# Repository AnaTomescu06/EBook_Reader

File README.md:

# OpenBook – Proiect TSC 2025

## Descriere generală

**OpenBook** este un dispozitiv portabil de tip e-book reader, conceput ca soluție open-source, eficientă energetic și scalabilă. Acesta se bazează pe microcontrolerul **ESP32-C6-WROOM**, având ca funcții principale afișarea de conținut pe un ecran e-paper și monitorizarea parametrilor de mediu (temperatură, umiditate, CO2, particule).

Dispozitivul permite salvarea datelor colectate pe un card microSD și oferă control prin intermediul unor butoane fizice.

## Diagramă bloc

## Funcționalitate hardware

Dispozitivul este structurat în jurul modulului **ESP32-C3-WROOM**, care gestionează toate interfețele de comunicare cu componentele externe.

### ESP32-C3-WROOM
- Microcontroler principal cu suport pentru **Wi-Fi** și **BLE**
- Interfețe: **SPI**, **I2C**, **UART**
- Alimentare: **3.3V** prin LDO

### Sistem de alimentare
- **USB-C** pentru alimentare externă și comunicare
- **MCP73832** pentru managementul încărcării bateriei Li-Po
- **LDO 3.3V** pentru alimentarea logicii
- **DC-DC 5V** pentru alimentarea senzorilor PM și CO2

### Senzori
- **BME680** (I2C, 3.3V) - temperatură, umiditate, gaze
- **MH-Z19B** (UART, 5V) - CO2
- **PMSA003** (UART, 5V) - particule fine (PM2.5)

### Ecran
- **E-paper monocrom 1.5''** cu rezoluție 200x200 px
- Interfață SPI comună cu cardul SD

### Card SD
- Slot microSD pentru stocarea de date/text
- Interfață SPI

### Butoane
- 3 butoane tactile conectate la pinii GPIO pentru interacțiune cu utilizatorul

## Bill of Materials (BOM)

| Part | Device | Datasheet |
|------|--------|-----------|
| CHG_LED | ADAFRUIT_LEDCHIP-LED0603 | [ADAFRUIT_LEDCHIP-LED0603](https://www.snapeda.com/parts/KP-1608SURCK/Kingbright/view-part/?ref=search&t=LED%200603) |
| SJ1 | SJ | [SJ](https://grabcad.com/library/solder-jumpers-1) |
| EPD_C5 | EAGLE-LTSPICE_CC0402 | [EAGLE-LTSPICE_CC0402](https://www.snapeda.com/parts/PGB1010603MR/Littelfuse/view-part/?ref=eda) |
| R3 | ESP32_WROVER_EAGLE-LTSPICE_RR0402 | (https://componentsearchengine.com/part-view/R0402%201%25%20100%20K%20(RC0402FR-07100KL)/YAGEO) |
| R1_PWRUSB | ESP32_WROVER_EAGLE-LTSPICE_RR0402 | (https://componentsearchengine.com/part-view/R0402%201%25%20100%20K%20(RC0402FR-07100KL) |
| C4_USB | EAGLE-LTSPICE_CC0402 | [EAGLE-LTSPICE_CC0402](https://componentsearchengine.com/part-view/CC0402MRX5R5BB106/YAGEO) |
| C1, C2, C6, C8, C9, C10, C_DELAY | ESP32_WROVER_EAGLE-LTSPICE_CC0402 | [ESP32_WROVER_EAGLE-LTSPICE_CC0402](https://componentsearchengine.com/part-view/CC0402MRX5R5BB106/YAGEO) |
| C3 | RCL_CPOL-EUCT3528 | [RCL_CPOL-EUCT3528](https://componentsearchengine.com/part-view/CC0402MRX5R5BB106/YAGEO) |
| R1, R1_PINH, R1_PINH1, R2_PINH, R2_PINH1, R4, R5, R6, R7, R8, R9, R10, R_BOOT, R_CHANGE, R_CL1, R_RESET | ESP32_WROVER_EAGLE-LTSPICE_RR0402 | [ESP32_WROVER_EAGLE-LTSPICE_RR0402](https://componentsearchengine.com/part-view/R0402%201%25%20100%20K%20(RC0402FR-07100KL)/YAGEO) |
| C7 | ESP32_WROVER_EAGLE-LTSPICE_CC0402 | [ESP32_WROVER_EAGLE-LTSPICE_CC0402](https://componentsearchengine.com/part-view/CC0402MRX5R5BB106/YAGEO) |
| J4 | 112A-TAAR-R03_ATTEND | [112A-TAAR-R03_ATTEND](https://store.comet.srl.ro/Catalogue/Product/43497/) |
| R_CAPACITOR | ESP32_WROVER_EAGLE-LTSPICE_RR0402 | [ESP32_WROVER_EAGLE-LTSPICE_RR0402](https://componentsearchengine.com/part-view/R0402%201%25%20100%20K%20(RC0402FR-07100KL)/YAGEO) |
| C5 | ESP32_WROVER_EAGLE-LTSPICE_CC0402 | [ESP32_WROVER_EAGLE-LTSPICE_CC0402](https://componentsearchengine.com/part-view/CC0402MRX5R5BB106/YAGEO) |
| EPD_C6, EPD_C7, EPD_C8, EPD_C9, EPD_C10, EPD_C11, EPD_C12 | EAGLE-LTSPICE_CC0402 | [EAGLE-LTSPICE_CC0402](https://componentsearchengine.com/part-view/CC0402MRX5R5BB106/YAGEO) |
| EPD_C1, EPD_C2 | ESP32_WROVER_EAGLE-LTSPICE_CC0402 | [ESP32_WROVER_EAGLE-LTSPICE_CC0402](https://componentsearchengine.com/part-view/CC0402MRX5R5BB106/YAGEO) |
| R2 | ESP32_WROVER_EAGLE-LTSPICE_RR0402 | [ESP32_WROVER_EAGLE-LTSPICE_RR0402](https://componentsearchengine.com/part-view/R0402%201%25%20100%20K%20(RC0402FR-07100KL)/YAGEO) |
| R1_BAT | ESP32_WROVER_EAGLE-LTSPICE_RR0402 | [ESP32_WROVER_EAGLE-LTSPICE_RR0402](https://componentsearchengine.com/part-view/R0402%201%25%20100%20K%20(RC0402FR-07100KL)/YAGEO) |
| Q1, Q2 | ESP32_WROVER_SPARKFUN-DISCRETESEMI_MOSFET_PCH-DMG2305UX-7 | [ESP32_WROVER_SPARKFUN-DISCRETESEMI_MOSFET_PCH-DMG2305UX-7](https://componentsearchengine.com/part-view/DMG2305UX-7/Diodes%20Incorporated) |
| R2_BAT | ESP32_WROVER_EAGLE-LTSPICE_RR0402 | [ESP32_WROVER_EAGLE-LTSPICE_RR0402](https://componentsearchengine.com/part-view/R0402%201%25%20100%20K%20(RC0402FR-07100KL)/YAGEO) |
| C5_USB | EAGLE-LTSPICE_CC0402 | [EAGLE-LTSPICE_CC0402](https://componentsearchengine.com/part-view/CC0402MRX5R5BB106/YAGEO) |
| C1_BAT, C1_BAT1, C1_BAT2, C2_BAT | ESP32_WROVER_EAGLE-LTSPICE_CC0402 | [ESP32_WROVER_EAGLE-LTSPICE_CC0402](https://componentsearchengine.com/part-view/CC0402MRX5R5BB106/YAGEO) |
| C4 | ESP32_WROVER_EAGLE-LTSPICE_CC0402 | [ESP32_WROVER_EAGLE-LTSPICE_CC0402](https://componentsearchengine.com/part-view/CC0402MRX5R5BB106/YAGEO) |
| R2-USB, R2-USB1 | ESP32_WROVER_EAGLE-LTSPICE_RR0402 | [ESP32_WROVER_EAGLE-LTSPICE_RR0402](https://componentsearchengine.com/part-view/R0402%201%25%20100%20K%20(RC0402FR-07100KL)/YAGEO) |
| L1 | 744043680IND_4828-WE-TPC_WRE | [744043680IND_4828-WE-TPC_WRE](https://eu.mouser.com/ProductDetail/Wurth-Elektronik/744043680?qs=PGXP4M47uW6VkZq%252BkzjrHA%3D%3D) |
| IC1 | BD5229G-TR | [BD5229G-TR](https://componentsearchengine.com/part-view/BD5229G-TR/ROHM%20Semiconductor) |
| SENSOR2 | ESP32_WROVER_BME680_BME680 | [ESP32_WROVER_BME680_BME680](https://www.snapeda.com/parts/BME680/Bosch/view-part/?welcome=home) |
| BUTTON_CUSYOMV1 |BUTTON_CUSYOMV1 | [BUTTON_CUSYOMV1](https://industry.panasonic.com/global/en/products/control/switch/light-touch/number/evqpuj02k) |
| C10_SUPERCAP | CPH3225A | [CPH3225A](https://www.snapeda.com/parts/CPH3225A/Seiko+Instruments/view-part/?ref=snap) |
| U3 | DS3231SN# | [DS3231SN#](https://www.snapeda.com/parts/DS3231SN%23/Analog+Devices/view-part/?ref=snap) |
| U2 | ESP32-C6-WROOM-1-N8 | [ESP32-C6-WROOM-1-N8](https://www.snapeda.com/parts/ESP32-C6-WROOM-1-N8/Espressif+Systems/view-part/?ref=eda) |
| PFMF.050.1 | ESP32C6_VARISTORCN1812 | [ESP32C6_VARISTORCN1812](https://www.mouser.co.uk/ProductDetail/EPCOS-TDK/B72520T0350K062?qs=dEfas%2FXlABIszF52uu7vrg%3D%3D) |
| D2, D7 | ESP32_WROVER_AVX---SD0805S020S1R0_AVX_SD0805S020S1R0_0_0AVX_SD0805S020S1R0_0_0 | [ESP32_WROVER_AVX---SD0805S020S1R0_AVX_SD0805S020S1R0_0_0AVX_SD0805S020S1R0_0_0](https://eu.mouser.com/ProductDetail/KYOCERA-AVX/SD0805S020S1R0?qs=jCA%252BPfw4LHbpkAoSnwrdjw%3D%3D) |
| U5 | ESP32_WROVER_SPARKFUN-IC-POWER_MCP73831 | [ESP32-C6-WROOM-1-N8](https://componentsearchengine.com/part-view/MCP73831T-2ATI%2FOT/Microchip) |
| J1 | FH34SRJ-24S-0.5SH_99_ | [FH34SRJ-24S-0.5SH_99_](https://componentsearchengine.com/part-view/XC6220A331MR-G/Torex) |
| U4 | MAX17048G+T10 | [MAX17048G+T10](https://www.snapeda.com/parts/MAX17048G+T10/Analog+Devices/view-part/?ref=snap) |
| D3, D4, D5 | MBR0530 | [MBR0530](https://www.snapeda.com/parts/MBR0530/Onsemi/view-part/?ref=snap) |
| D6, D8, D9, D10, D11, D12 | PGB1010603MR | [PGB1010603MR](https://www.snapeda.com/parts/PGB1010603MR/Littelfuse/view-part/?ref=snap) |
| J3 | QWIIC_CONNECTORJS-1MM | [QWIIC_CONNECTORJS-1MM](https://www.snapeda.com/parts/PRT-14417/SparkFun%20Electronics/view-part/?ref=search&t=qwiic) |
| J2 | SAMACSYS_PARTS_USB4110-GF-A | (https://componentsearchengine.com/part-view/USB4110-GF-A/GCT%20(GLOBAL%20CONNECTOR%20TECHNOLOGY) |
| Q3 | SI1308EDL-T1-GE3 | [SI1308EDL-T1-GE3](https://componentsearchengine.com/part-view/SI1308EDL-T1-GE3/Vishay) |
| TP1, TP2, TP3, TP4, TP5, TP6, TP7, TP8, TP9, TP10, TP11, TP12, TP13, TP14, TP15, TP16, TP17 | TPTP20R | [facute de mine] |
| D1 | USBLC6-2SC6Y | [USBLC6-2SC6Y](https://www.snapeda.com/parts/USBLC6-2SC6Y/STMicroelectronics/view-part/?ref=snap) |
| U1 | W25Q512JVEIQ | [W25Q512JVEIQ](https://www.snapeda.com/parts/W25Q512JVEIQ/Winbond+Electronics/view-part/?ref=snap) |
| IC4 | XC6220A331MR-G | [XC6220A331MR-G](https://componentsearchengine.com/part-view/XC6220A331MR-G/Torex) |

## Alocare pini ESP32-C3

| Pin ESP32-C3 | Componentă  | Funcție / Motiv                     |
|--------------|-------------|-------------------------------------|
| GPIO1        | BME680      | I2C - SDA                           |
| GPIO2        | BME680      | I2C - SCL                           |
| GPIO3        | PMSA003     | UART RX pentru senzor PM           |
| GPIO4        | SD Card     | SPI Chip Select (CS)               |
| GPIO5        | E-Ink       | Data/Command                       |
| GPIO6        | E-Ink & SD  | SPI Clock (SCK)                    |
| GPIO7        | E-Ink & SD  | SPI MOSI (date)                    |
| GPIO8        | Buton 1     | Control meniu / pagină             |
| GPIO9        | Buton 2     | Control meniu / pagină             |
| GPIO10       | E-Ink       | SPI Chip Select (CS)               |
| GPIO11       | Flash ext.  | CS rezervat, neutilizat momentan   |
| GPIO12       | USB         | USB D-                             |
| GPIO13       | USB         | USB D+                             |
| GPIO18       | MH-Z19B     | UART TX pentru senzor CO2          |
| GPIO19       | Buton 3     | Confirmare / acțiune suplimentară  |

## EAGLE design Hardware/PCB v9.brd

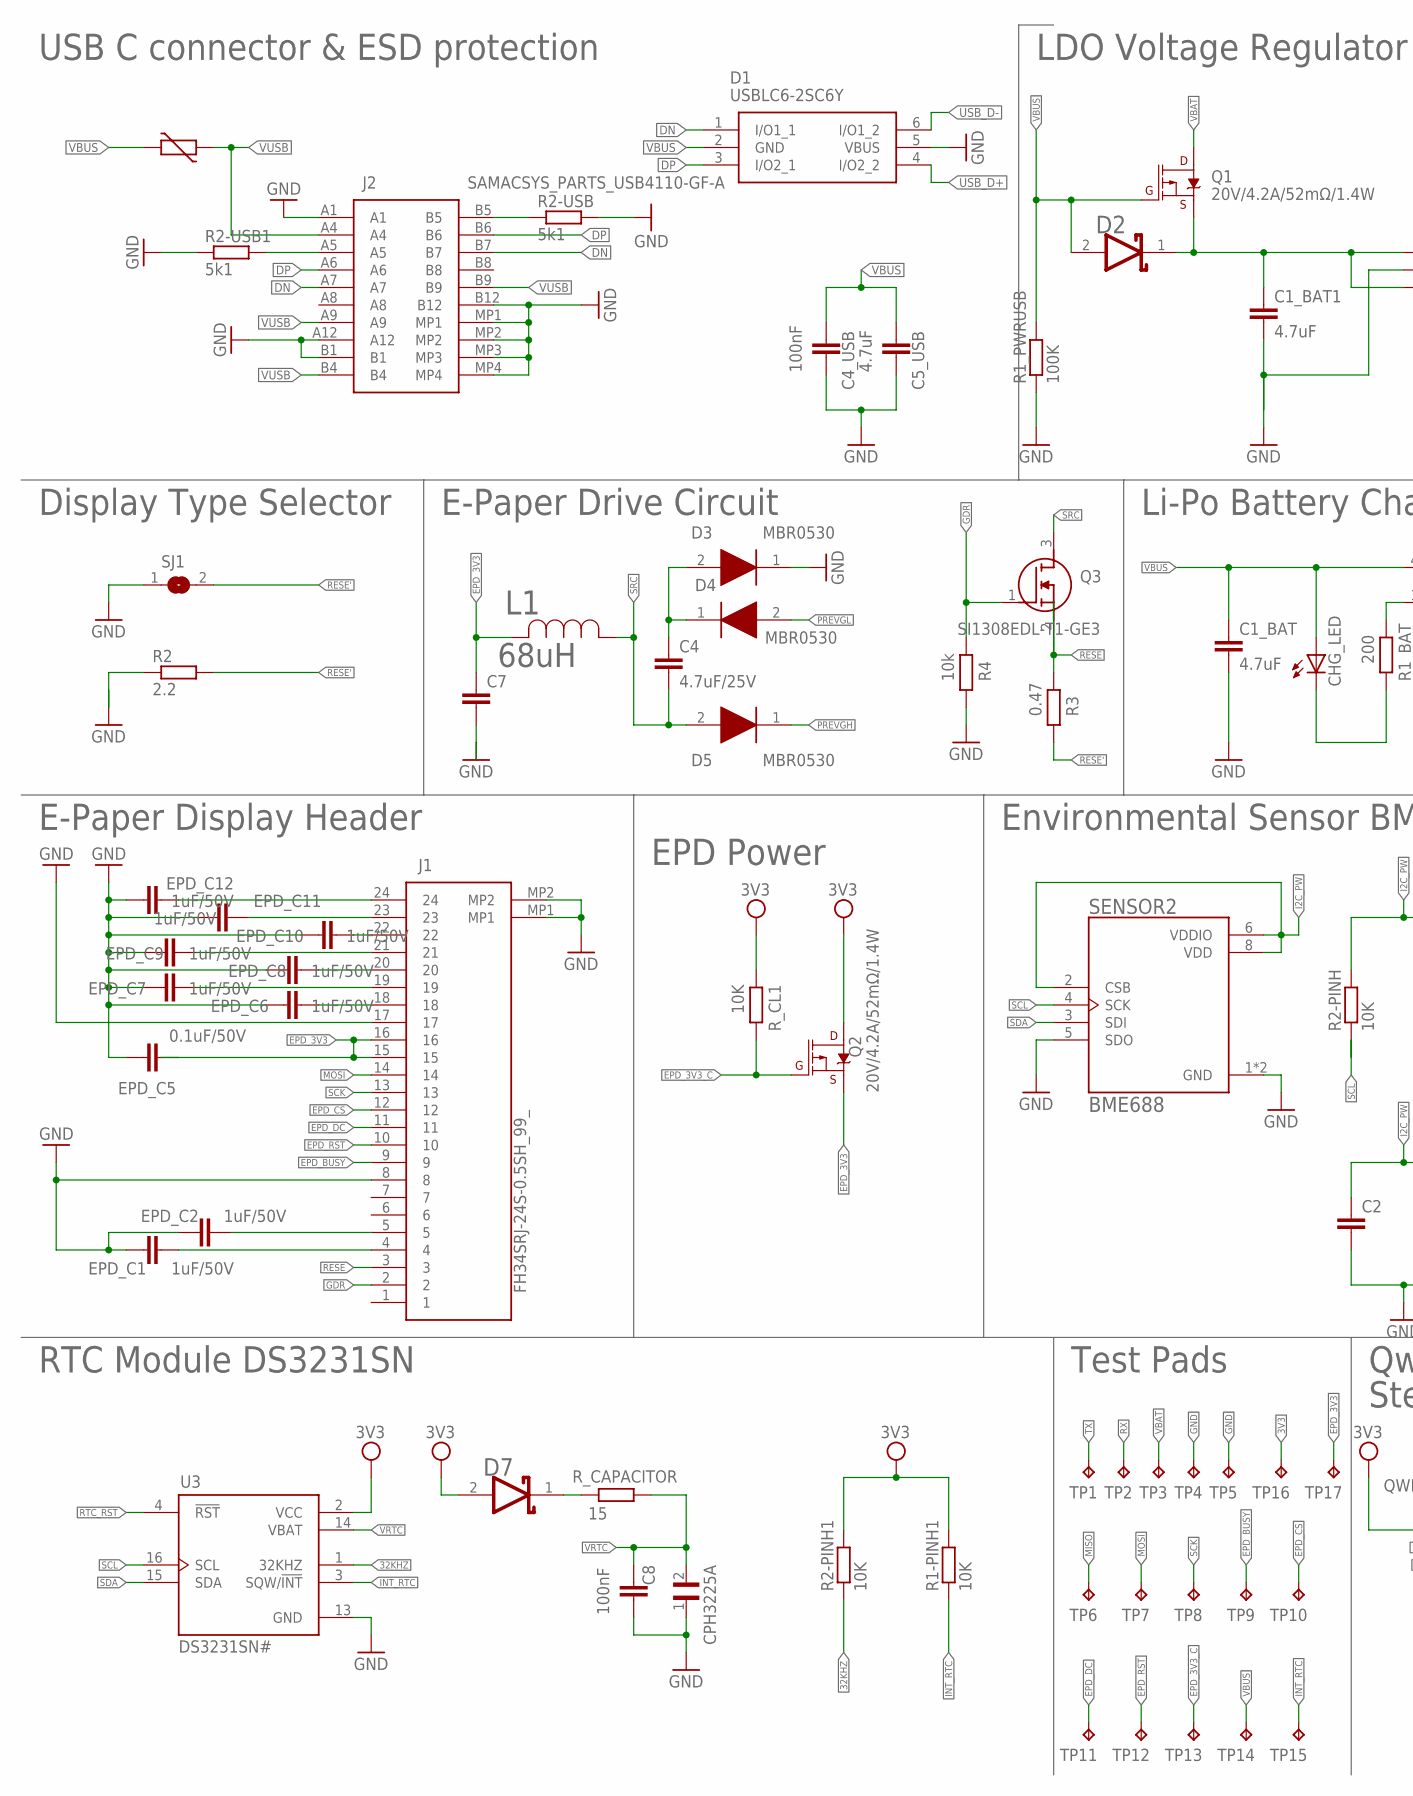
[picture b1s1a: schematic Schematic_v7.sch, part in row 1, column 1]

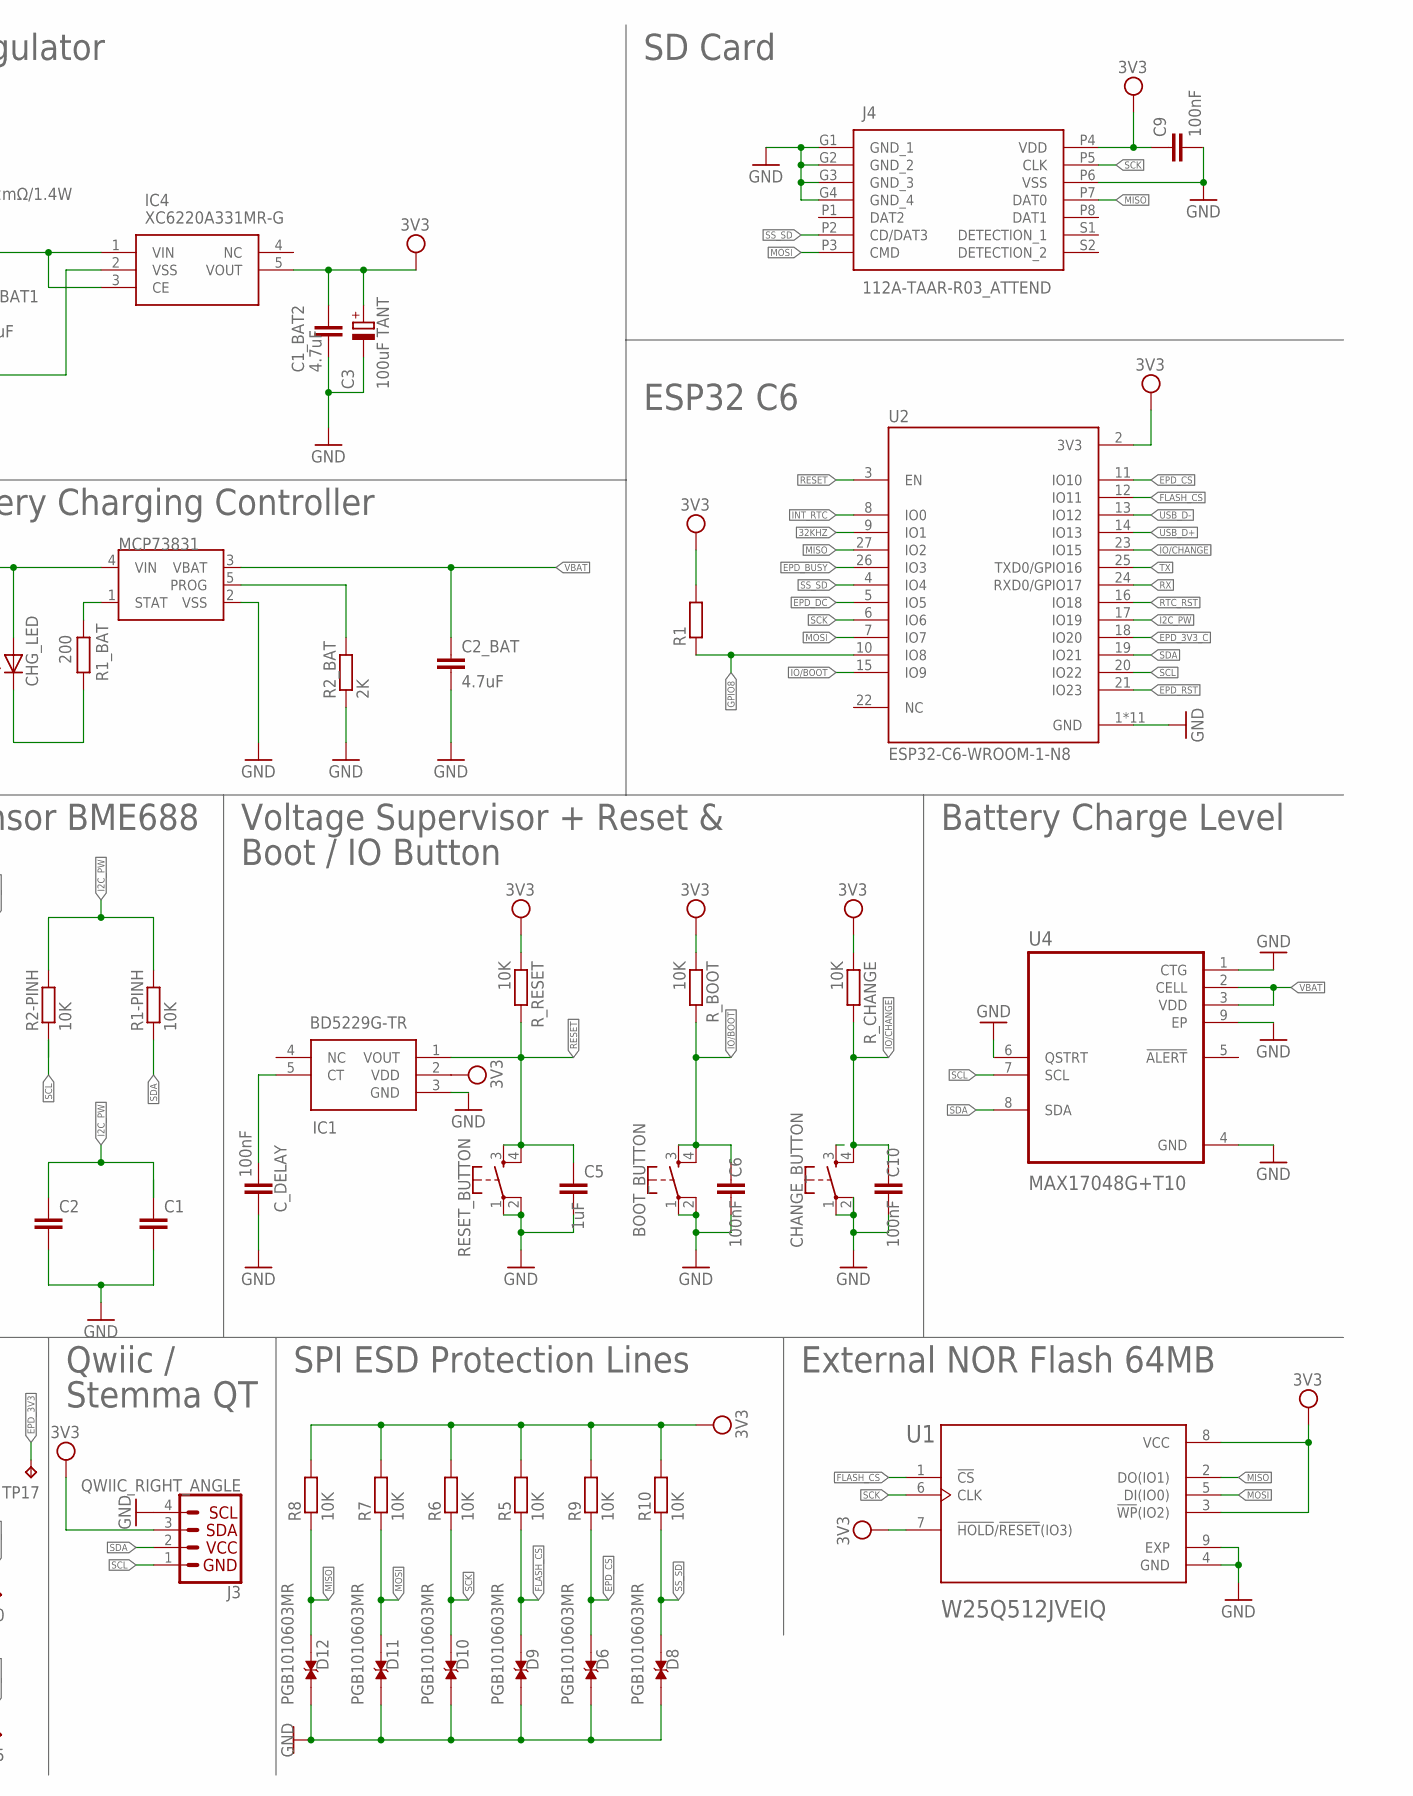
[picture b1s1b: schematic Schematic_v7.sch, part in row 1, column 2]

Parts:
BOOT_BUTTON: BUTTON_CUSYOMV1; MYBUTTON
C1, C2, C7: EAGLE-LTSPICE_CC0402; EAGLE-LTSPICE_C0402
C1_BAT, C5_USB: 4.7uF; ESP32_WROVER_EAGLE-LTSPICE_C0402
C1_BAT1, C1_BAT2, C2_BAT: 4.7uF; EAGLE-LTSPICE_C0402
C3: 100uF TANT; RCL_CT3528
C4: 4.7uF/25V; ESP32_WROVER_EAGLE-LTSPICE_C0402
C4_USB: 100nF; ESP32_WROVER_EAGLE-LTSPICE_C0402
C5: 1uF; EAGLE-LTSPICE_C0402
C6, C9, C10, C11: 100nF; EAGLE-LTSPICE_C0402
C8: CPH3225A; CAPCP3225X100N
CHANGE_BUTTON: BUTTON_CUSYOMV1; MYBUTTON
CHG_LED: ADAFRUIT_LEDCHIP-LED0603; ADAFRUIT_CHIP-LED0603
C_DELAY: 100nF; EAGLE-LTSPICE_C0402
D1: USBLC6-2SC6Y; SOT95P280X145-6N
D2, D7: ESP32_WROVER_AVX---SD0805S020S1R0_AVX_SD0805S020S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; ESP32_WROVER_AVX---SD0805S020S1R0_AVX_SD0805S020S1R0_0
D3, D4, D5: MBR0530; SOD3716X135N
D6, D8, D9, D10, D11, D12: PGB1010603MR; DIOC1608X36N
EPD_C1, EPD_C2, EPD_C6, EPD_C7, EPD_C8, EPD_C9, EPD_C10, EPD_C11, EPD_C12: 1uF/50V; ESP32_WROVER_EAGLE-LTSPICE_C0402
EPD_C5: 0.1uF/50V; EAGLE-LTSPICE_C0402
IC1: BD5229G-TR; SOT95P280X125-5N
IC4: XC6220A331MR-G; SOT95P280X120-5N
J1: FH34SRJ-24S-0.5SH_99_; FH34SRJ24S05SH99
J2: SAMACSYS_PARTS_USB4110-GF-A; SAMACSYS_PARTS_USB4110GFA
J3: QWIIC_RIGHT_ANGLE; JST04_1MM_RA
J4: 112A-TAAR-R03_ATTEND; 112ATAARR03ATTEND
L1: 68uH; IND_4828-WE-TPC_WRE
PFMF.050.1: ESP32C6_VARISTORCN1812; ESP32C6_VARISTOR_CT/CN1812
Q1, Q2: 20V/4.2A/52mΩ/1.4W; ESP32_WROVER_SPARKFUN-DISCRETESEMI_SOT23-3
Q3: SI1308EDL-T1-GE3; SOT65P210X110-3N
R1: ESP32_WROVER_EAGLE-LTSPICE_RR0402; ESP32_WROVER_EAGLE-LTSPICE_R0402
R1-PINH, R1-PINH1, R2-PINH, R2-PINH1, R5, R6, R7, R8, R9, R10: 10K; ESP32_WROVER_EAGLE-LTSPICE_R0402
R1_BAT: 200; ESP32_WROVER_EAGLE-LTSPICE_R0402
R1_PWRUSB: 100K; ESP32_WROVER_EAGLE-LTSPICE_R0402
R2: 2.2; ESP32_WROVER_EAGLE-LTSPICE_R0402
R2-USB, R2-USB1: 5k1; ESP32_WROVER_EAGLE-LTSPICE_R0402
R2_BAT: 2K; ESP32_WROVER_EAGLE-LTSPICE_R0402
R3: 0.47; ESP32_WROVER_EAGLE-LTSPICE_R0402
R4: 10k; ESP32_WROVER_EAGLE-LTSPICE_R0402
RESET_BUTTON: BUTTON_CUSYOMV1; MYBUTTON
R_BOOT: 10K; ESP32_WROVER_EAGLE-LTSPICE_R0402
R_CAPACITOR: 15; ESP32_WROVER_EAGLE-LTSPICE_R0402
R_CHANGE: 10K; ESP32_WROVER_EAGLE-LTSPICE_R0402
R_CL1: 10K; ESP32_WROVER_EAGLE-LTSPICE_R0402
R_RESET: 10K; ESP32_WROVER_EAGLE-LTSPICE_R0402
SENSOR2: BME688; ESP32_WROVER_BME680_PSON80P300X300X100-8N
SJ1: SJ
TP1, TP2, TP3, TP4, TP5, TP6, TP7, TP8, TP9, TP10, TP11, TP12, TP13, TP14, TP15, TP16, TP17: TPTP20R; TP20R
U1: W25Q512JVEIQ; SON127P600X800X80-9N
U2: ESP32-C6-WROOM-1-N8; XCVR_ESP32-C6-WROOM-1-N8
U3: DS3231SN#; SOIC127P1032X265-16N
U4: MAX17048G+T10; SON50P200X200X80-9N
U6: MCP73831; ESP32_WROVER_SPARKFUN-IC-POWER_SOT23-5

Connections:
3V3: C1_BAT2.1, C3.+, C9.1, D7.2 (ANODE), IC1.2 (VDD), IC4.5 (VOUT), J3.3, J4.P4 (VDD), Q2.3 (D), R1.2, R1-PINH1.2, R2-PINH1.2, R5.2, R6.2, R7.2, R8.2, R9.2, R10.2, R_BOOT.1, R_CHANGE.1, R_CL1.2, R_RESET.1, TP16.TP, U1.3 (!WP!(IO2)), U1.7 (!HOLD!/!RESET!(IO3)), U1.8 (VCC), U2.2 (3V3), U3.2 (VCC)
32KHZ: R2-PINH1.1, U2.9 (IO1), U3.1 (32KHZ)
DN: D1.1 (I/O1_1), J2.A7, J2.B7
DP: D1.3 (I/O2_1), J2.A6, J2.B6
EPD_3V3: C7.1, EPD_C5.2, J1.15, J1.16, L1.2, Q2.2 (S), TP17.TP
EPD_3V3_C: Q2.1 (G), R_CL1.1, TP13.TP, U2.18 (IO20)
EPD_BUSY: J1.9, TP9.TP, U2.26 (IO3)
EPD_CS: D6.2, J1.12, R9.1, TP10.TP, U2.11 (IO10)
EPD_DC: J1.11, TP11.TP, U2.5 (IO5)
EPD_RST: J1.10, TP12.TP, U2.21 (IO23)
FLASH_CS: D9.2, R5.1, U1.1 (!CS), U2.12 (IO11)
GDR: J1.2, Q3.1 (G), R4.2
GND: BOOT_BUTTON.1, BOOT_BUTTON.2, C1.2, C1_BAT.2, C1_BAT1.2, C1_BAT2.2, C2.2, C2_BAT.2, C3.-, C4_USB.2, C5.2, C5_USB.2, C6.2, C7.2, C8.1, C9.2, C10.2, C11.2, CHANGE_BUTTON.1, CHANGE_BUTTON.2, C_DELAY.2, D1.5 (VBUS), D3.1 (K), EPD_C1.2, EPD_C2.2, EPD_C5.1, EPD_C6.2, EPD_C7.2, EPD_C8.2, EPD_C9.2, EPD_C10.2, EPD_C11.2, EPD_C12.2, IC1.3 (GND), IC4.2 (VSS), J1.8, J1.17, J1.MP1, J1.MP2, J2.A1, J2.A12, J2.B1, J2.B12, J2.MP1, J2.MP2, J2.MP3, J2.MP4, J3.4, J4.G1 (GND_1), J4.G2 (GND_2), J4.G3 (GND_3), J4.G4 (GND_4), J4.P6 (VSS), R1_PWRUSB.1, R2.1, R2-USB.2, R2-USB1.1, R2_BAT.1, R4.1, RESET_BUTTON.1, RESET_BUTTON.2, SENSOR2.1 (GND), SENSOR2.5 (SDO), SENSOR2.7 (GND), SJ1.1, TP4.TP, TP5.TP, U1.4 (GND), U1.9 (EXP), U2.1 (GND), U2.28 (GND), U2.29_1 (GND), U2.29_2 (GND), U2.29_3 (GND), U2.29_4 (GND), U2.29_5 (GND), U2.29_6 (GND), U2.29_7 (GND), U2.29_8 (GND), U2.29_9 (GND), U3.13 (GND), U4.1 (CTG), U4.4 (GND), U4.6 (QSTRT), U4.9 (EP), U6.2 (VSS)
GPIO8: R1.1, U2.10 (IO8)
I2C_PW: C1.1, C2.1, R1-PINH.2, R2-PINH.2, SENSOR2.2 (CSB), SENSOR2.6 (VDDIO), SENSOR2.8 (VDD), U2.17 (IO19)
INT_RTC: R1-PINH1.1, TP15.TP, U2.8 (IO0), U3.3 (SQW/!INT)
IO/BOOT: BOOT_BUTTON.3, BOOT_BUTTON.4, C6.1, R_BOOT.2, U2.15 (IO9)
IO/CHANGE: C10.1, CHANGE_BUTTON.4, R_CHANGE.2, U2.23 (IO15)
MISO: D6.1, D8.1, D9.1, D10.1, D11.1, D12.1, D12.2, J4.P7 (DAT0), R8.1, TP6.TP, U1.2 (DO(IO1)), U2.27 (IO2)
MOSI: D11.2, J1.14, J4.P3 (CMD), R7.1, TP7.TP, U1.5 (DI(IO0)), U2.7 (IO7)
unnamed: J2.A5, R2-USB1.2
unnamed: J2.B5, R2-USB.1
unnamed: C1_BAT1.1, D2.1 (CATHODE), IC4.1 (VIN), IC4.3 (CE), Q1.2 (S)
unnamed: C4.1, D3.2 (A), D4.1 (K)
unnamed: CHG_LED.C, R1_BAT.1
unnamed: R1_BAT.2, U6.1 (STAT)
unnamed: EPD_C12.1, J1.24
unnamed: R2_BAT.2, U6.5 (PROG)
unnamed: EPD_C10.1, J1.22
unnamed: EPD_C11.1, J1.23
unnamed: EPD_C9.1, J1.21
unnamed: EPD_C8.1, J1.20
unnamed: EPD_C7.1, J1.19
unnamed: EPD_C2.1, J1.5
unnamed: EPD_C1.1, J1.4
unnamed: EPD_C6.1, J1.18
unnamed: C_DELAY.1, IC1.5 (CT)
unnamed: D7.1 (CATHODE), R_CAPACITOR.2
PREVGH: D5.1 (K)
PREVGL: D4.2 (A)
RESE: J1.3, Q3.2 (S), R3.2
RESE': R2.2, R3.1, SJ1.2
RESET: C5.1, IC1.1 (VOUT), RESET_BUTTON.3, RESET_BUTTON.4, R_RESET.2, U2.3 (EN)
RTC_RST: U2.16 (IO18), U3.4 (!RST)
RX: TP2.TP, U2.24 (RXD0/GPIO17)
SCK: D10.2, J1.13, J4.P5 (CLK), R6.1, TP8.TP, U1.6 (CLK), U2.6 (IO6)
SCL: J3.1, R2-PINH.1, SENSOR2.4 (SCK), U2.20 (IO22), U3.16 (SCL), U4.7 (SCL)
SDA: J3.2, R1-PINH.1, SENSOR2.3 (SDI), U2.19 (IO21), U3.15 (SDA), U4.8 (SDA)
SRC: C4.2, D5.2 (A), L1.1, Q3.3 (D)
SS_SD: D8.2, J4.P2 (CD/DAT3), R10.1, U2.4 (IO4)
TX: TP1.TP, U2.25 (TXD0/GPIO16)
USB_D+: D1.4 (I/O2_2), U2.14 (IO13)
USB_D-: D1.6 (I/O1_2), U2.13 (IO12)
VBAT: C2_BAT.1, Q1.3 (D), TP3.TP, U4.2 (CELL), U4.3 (VDD), U6.3 (VBAT)
VBUS: C1_BAT.1, C4_USB.1, C5_USB.1, CHG_LED.A, D1.2 (GND), D2.2 (ANODE), PFMF.050.1.2, Q1.1 (G), R1_PWRUSB.2, TP14.TP, U6.4 (VIN)
VRTC: C8.2, C11.1, R_CAPACITOR.1, U3.14 (VBAT)
VUSB: J2.A4, J2.A9, J2.B4, J2.B9, PFMF.050.1.1

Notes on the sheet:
USB C connector & ESD protection
LDO Voltage Regulator
SD Card
Display Type Selector
E-Paper Drive Circuit
Li-Po Battery Charging Controller
ESP32 C6
E-Paper Display Header
EPD Power
Environmental Sensor BME688
Voltage Supervisor + Reset &
Boot / IO Button
Battery Charge Level
RTC Module DS3231SN
Test Pads
Qwiic /
Stemma QT
SPI ESD Protection Lines
External NOR Flash 64MB

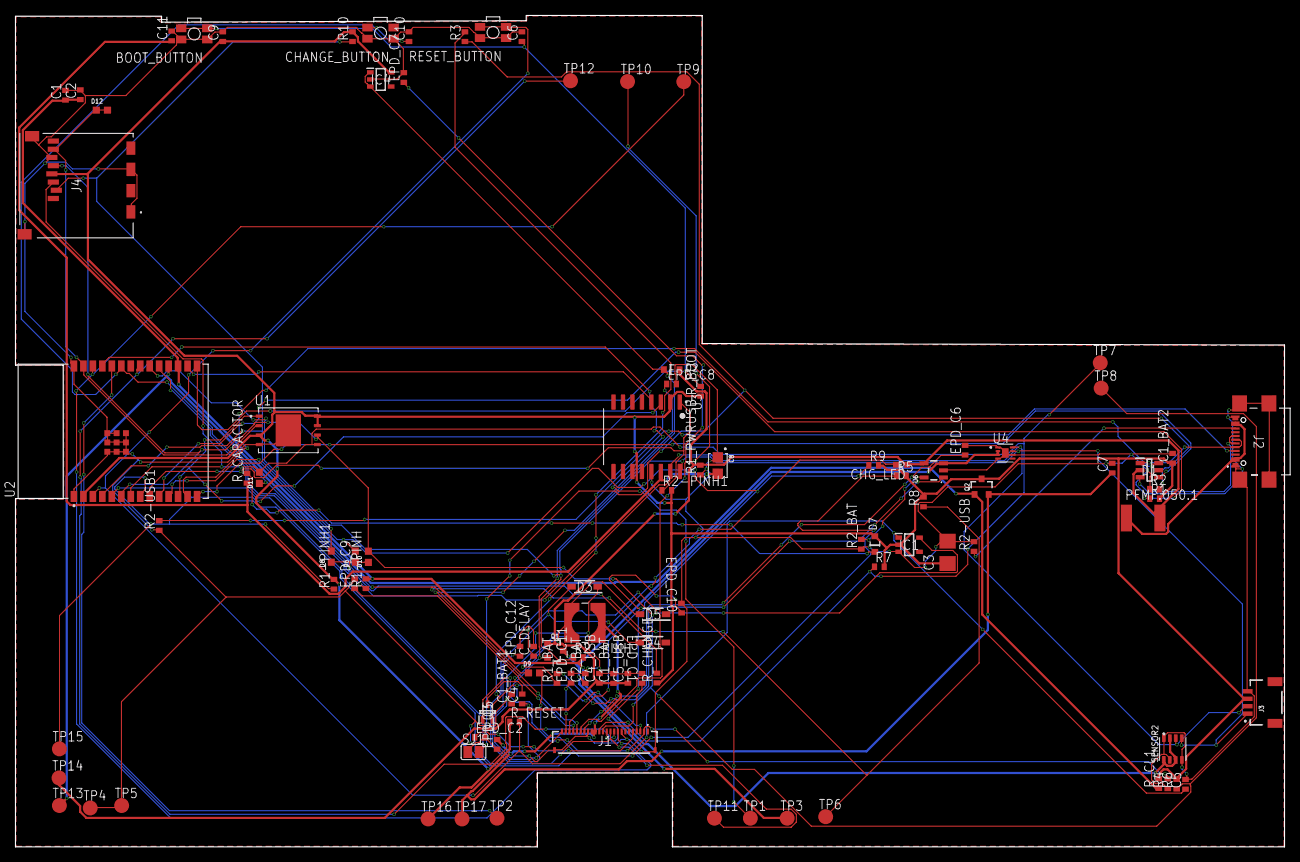
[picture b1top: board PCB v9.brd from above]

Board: 2 copper layers, 170.2 x 111.5 mm, 103 parts (0 on the bottom side), 55 nets.

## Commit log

2025-04-06 LICENSE
2025-04-06 README.md

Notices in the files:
parts and their libraries:
COPYRIGHT: Copyright (C) 2024 Ultra Librarian. All rights reserved.
